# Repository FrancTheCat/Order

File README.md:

# The-Extender
A 5x15 ortholinear keyboard powered by QMK

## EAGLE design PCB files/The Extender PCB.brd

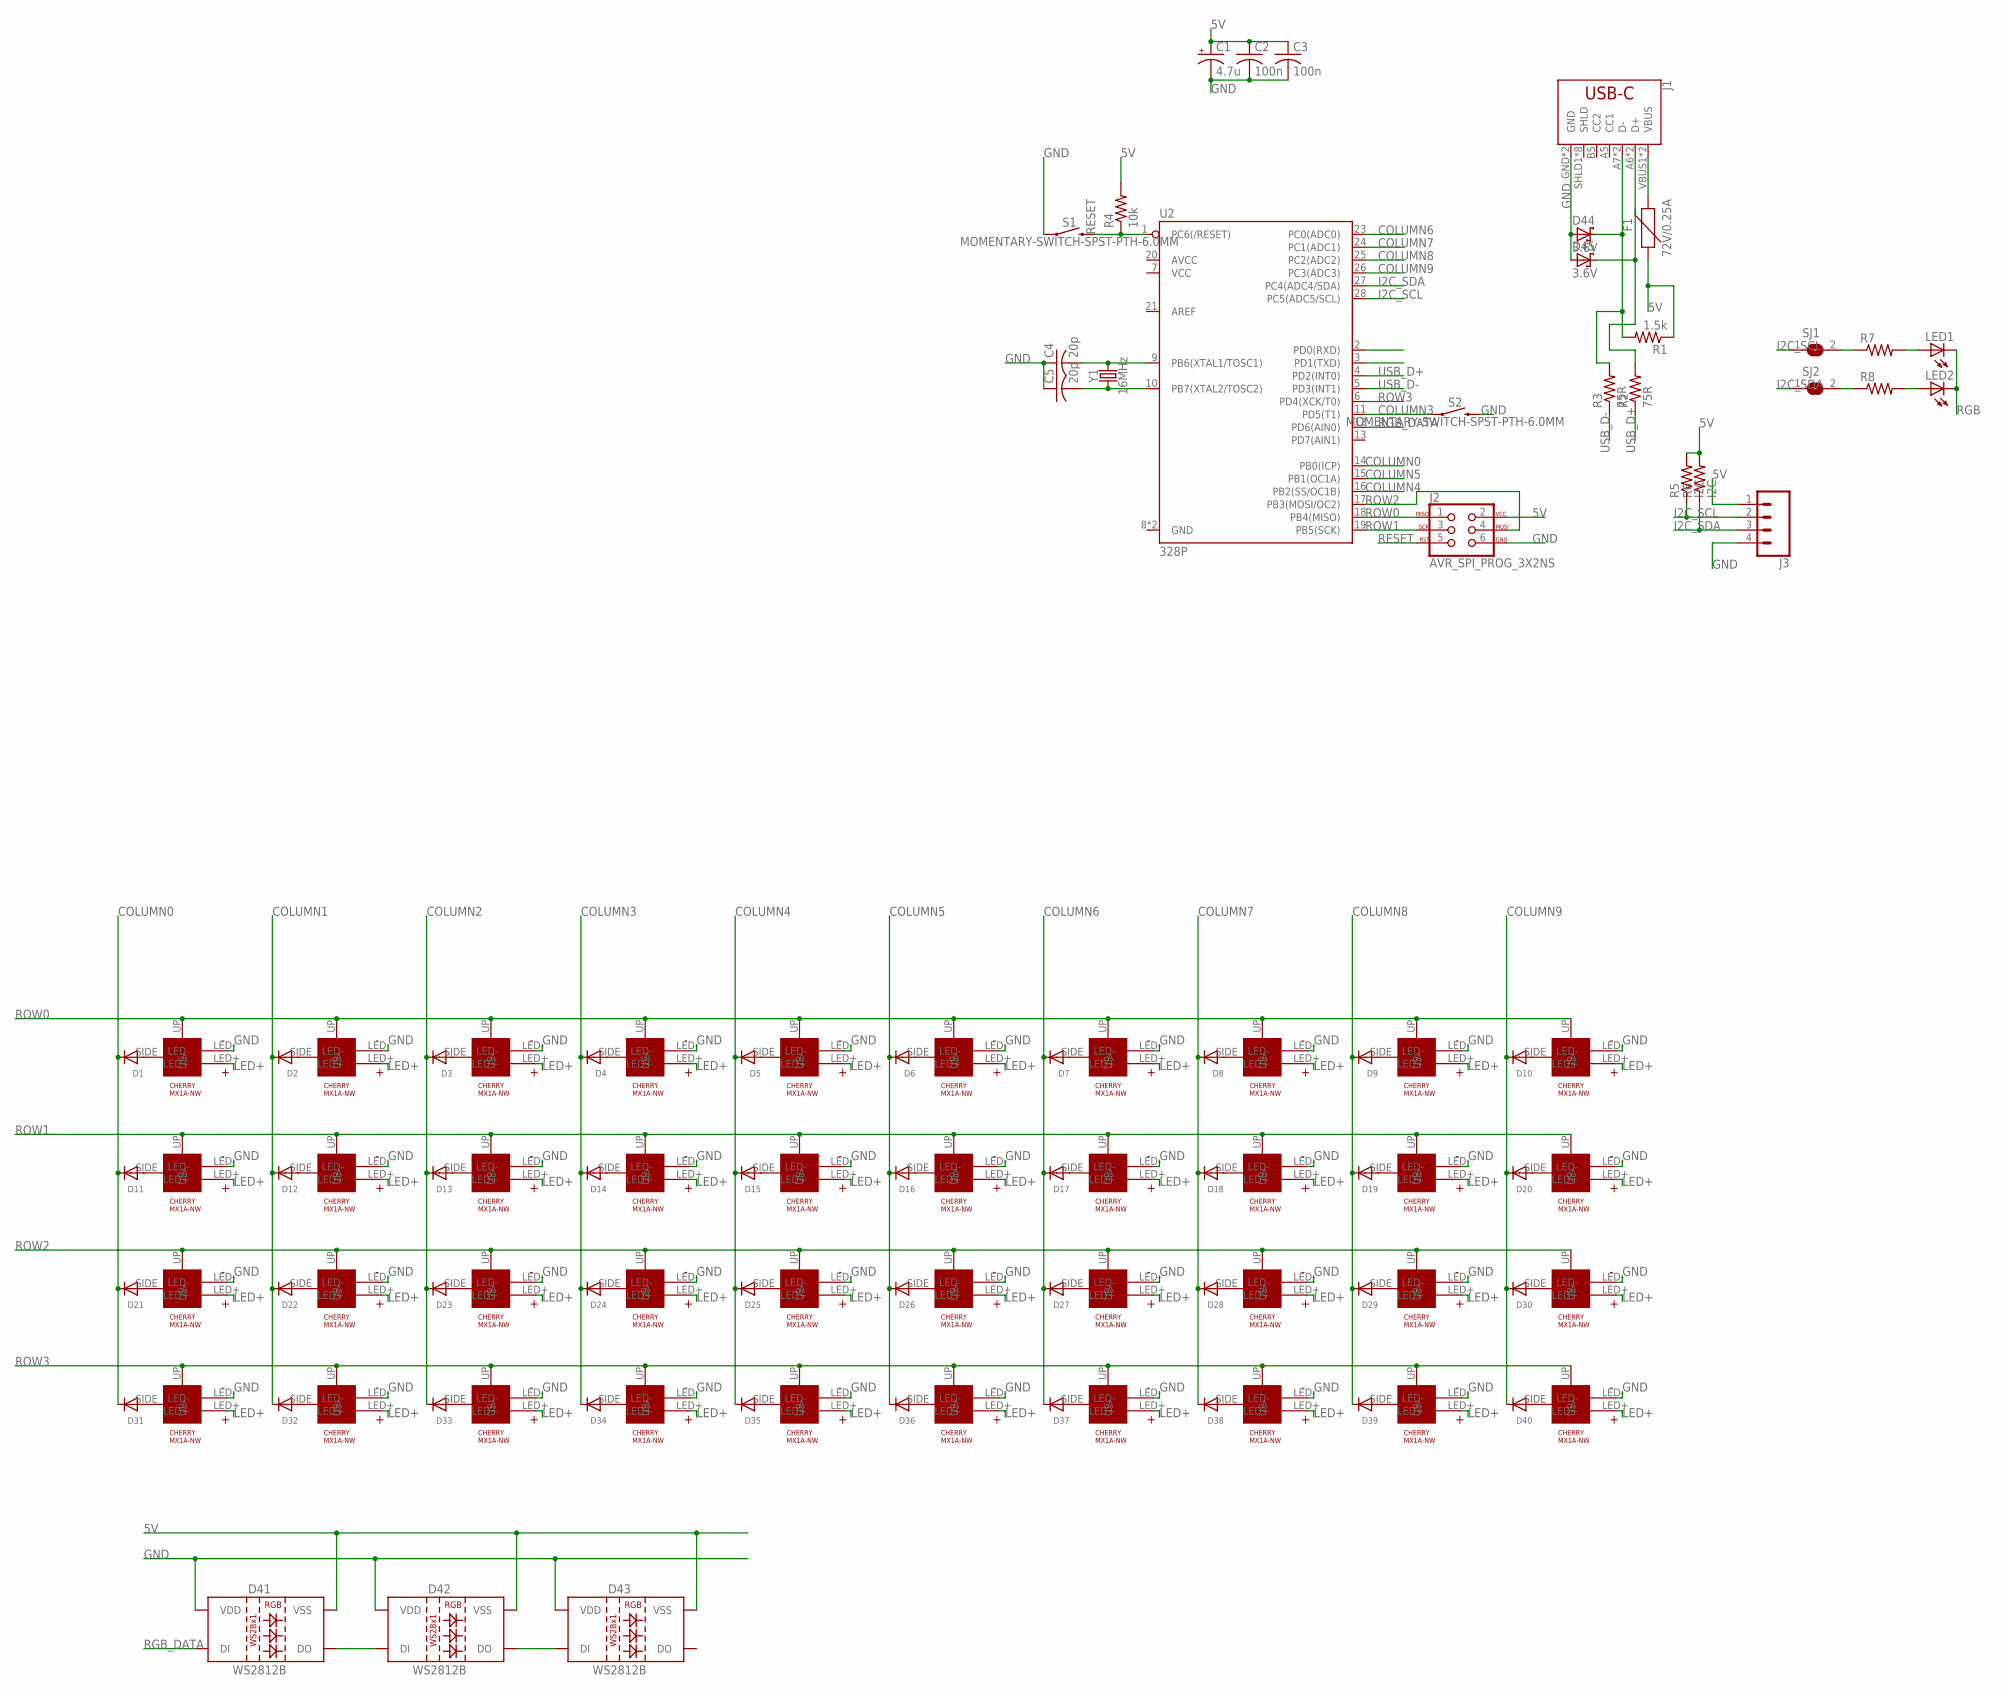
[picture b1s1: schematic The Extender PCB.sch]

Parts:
C1: 4.7u; E2,5-5
C2, C3: 100n; C050-025X075
C4, C5: 20p; C050-025X075
D1, D2, D3, D4, D5, D6, D7, D8, D9, D10, D11, D12, D13, D14, D15, D16, D17, D18, D19, D20, D21, D22, D23, D24, D25, D26, D27, D28, D29, D30, D31, D32, D33, D34, D35, D36, D37, D38, D39, D40: DIODEDO-1N4148; DO-1N4148
D41, D42, D43: WS2812B
D44, D45: 3.6V; DO41-7
F1: 72V/0.25A; PTH
J1: USB_C16PIN; USB-C-16P
J2: AVR_SPI_PROG_3X2NS; 2X3-NS
J3: CONN_04; 1X04
LED1, LED2: LED3MM
R1: 1.5k; 0207/7
R2, R3: 75R; 0207/7
R4: 10k; 0207/5V
R5, R6: I2C; 0207/5V
R7, R8: R-US_0207/5V; 0207/5V
S1, S2: MOMENTARY-SWITCH-SPST-PTH-6.0MM; TACTILE_SWITCH_PTH_6.0MM
SJ1, SJ2: SJ
U2: 328P; DIP28
U$1, U$2, U$3, U$4, U$5, U$6, U$7, U$8, U$9, U$10, U$11, U$12, U$13, U$14, U$15, U$16, U$17, U$18, U$19, U$20, U$21, U$22, U$23, U$24, U$25, U$26, U$27, U$28, U$29, U$30, U$31, U$32, U$33, U$34, U$35, U$36, U$37, U$38, U$39, U$40: CHERRY-MX1A-E1NW-LED; CHERRYMX-NN-LED
Y1: 16MHz; HC49US

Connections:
5V: C1.+, C2.1, C3.1, D41.3 (VSS), D42.3 (VSS), D43.3 (VSS), F1.P$1 (1), J2.2, J3.1, R1.1, R4.2, R5.2, R6.2
COLUMN0: D1.C, D11.C, D21.C, D31.C, U2.14 (PB0(ICP))
COLUMN1: D2.C, D12.C, D22.C, D32.C
COLUMN2: D3.C, D13.C, D23.C, D33.C
COLUMN3: D4.C, D14.C, D24.C, D34.C, S2.1, U2.11 (PD5(T1))
COLUMN4: D5.C, D15.C, D25.C, D35.C, U2.16 (PB2(SS/OC1B))
COLUMN5: D6.C, D16.C, D26.C, D36.C, U2.15 (PB1(OC1A))
COLUMN6: D7.C, D17.C, D27.C, D37.C, U2.23 (PC0(ADC0))
COLUMN7: D8.C, D18.C, D28.C, D38.C, U2.24 (PC1(ADC1))
COLUMN8: D9.C, D19.C, D29.C, D39.C, U2.25 (PC2(ADC2))
COLUMN9: D10.C, D20.C, D30.C, D40.C, U2.26 (PC3(ADC3))
GND: C1.-, C2.2, C3.2, C4.1, C5.1, D41.1 (VDD), D42.1 (VDD), D43.1 (VDD), D44.A, D45.A, J1.GND, J1.GND2 (GND), J2.6, J3.4, S1.1, S2.3 (2), U$1.LED-, U$2.LED-, U$3.LED-, U$4.LED-, U$5.LED-, U$6.LED-, U$7.LED-, U$8.LED-, U$9.LED-, U$10.LED-, U$11.LED-, U$12.LED-, U$13.LED-, U$14.LED-, U$15.LED-, U$16.LED-, U$17.LED-, U$18.LED-, U$19.LED-, U$20.LED-, U$21.LED-, U$22.LED-, U$23.LED-, U$24.LED-, U$25.LED-, U$26.LED-, U$27.LED-, U$28.LED-, U$29.LED-, U$30.LED-, U$31.LED-, U$32.LED-, U$33.LED-, U$34.LED-, U$35.LED-, U$36.LED-, U$37.LED-, U$38.LED-, U$39.LED-, U$40.LED-
I2C_SCL: J3.2, R5.1, SJ1.1, U2.28 (PC5(ADC5/SCL))
I2C_SDA: J3.3, R6.1, SJ2.1, U2.27 (PC4(ADC4/SDA))
LED+: U$1.LED+, U$2.LED+, U$3.LED+, U$4.LED+, U$5.LED+, U$6.LED+, U$7.LED+, U$8.LED+, U$9.LED+, U$10.LED+, U$11.LED+, U$12.LED+, U$13.LED+, U$14.LED+, U$15.LED+, U$16.LED+, U$17.LED+, U$18.LED+, U$19.LED+, U$20.LED+, U$21.LED+, U$22.LED+, U$23.LED+, U$24.LED+, U$25.LED+, U$26.LED+, U$27.LED+, U$28.LED+, U$29.LED+, U$30.LED+, U$31.LED+, U$32.LED+, U$33.LED+, U$34.LED+, U$35.LED+, U$36.LED+, U$37.LED+, U$38.LED+, U$39.LED+, U$40.LED+
unnamed: D1.A, U$1.SIDE (A)
unnamed: D2.A, U$2.SIDE (A)
unnamed: D3.A, U$3.SIDE (A)
unnamed: D4.A, U$4.SIDE (A)
unnamed: D5.A, U$5.SIDE (A)
unnamed: D6.A, U$6.SIDE (A)
unnamed: D7.A, U$7.SIDE (A)
unnamed: D8.A, U$8.SIDE (A)
unnamed: D9.A, U$9.SIDE (A)
unnamed: D10.A, U$10.SIDE (A)
unnamed: D11.A, U$11.SIDE (A)
unnamed: D12.A, U$12.SIDE (A)
unnamed: D13.A, U$13.SIDE (A)
unnamed: D14.A, U$14.SIDE (A)
unnamed: D15.A, U$15.SIDE (A)
unnamed: D16.A, U$16.SIDE (A)
unnamed: D17.A, U$17.SIDE (A)
unnamed: D18.A, U$18.SIDE (A)
unnamed: D19.A, U$19.SIDE (A)
unnamed: D20.A, U$20.SIDE (A)
unnamed: D21.A, U$21.SIDE (A)
unnamed: D22.A, U$22.SIDE (A)
unnamed: D23.A, U$23.SIDE (A)
unnamed: D24.A, U$24.SIDE (A)
unnamed: D25.A, U$25.SIDE (A)
unnamed: D26.A, U$26.SIDE (A)
unnamed: D27.A, U$27.SIDE (A)
unnamed: D28.A, U$28.SIDE (A)
unnamed: D29.A, U$29.SIDE (A)
unnamed: D30.A, U$30.SIDE (A)
unnamed: D31.A, U$31.SIDE (A)
unnamed: D32.A, U$32.SIDE (A)
unnamed: D33.A, U$33.SIDE (A)
unnamed: D34.A, U$34.SIDE (A)
unnamed: D35.A, U$35.SIDE (A)
unnamed: D36.A, U$36.SIDE (A)
unnamed: D37.A, U$37.SIDE (A)
unnamed: D38.A, U$38.SIDE (A)
unnamed: D39.A, U$39.SIDE (A)
unnamed: D40.A, U$40.SIDE (A)
unnamed: D41.2 (DO), D42.4 (DI)
unnamed: D42.2 (DO), D43.4 (DI)
unnamed: F1.P$2 (2), J1.VBUS1 (VBUS), J1.VBUS2 (VBUS)
unnamed: D44.C, J1.A7 (D-), J1.B7 (D-), R1.2, R3.2
unnamed: D45.C, J1.A6 (D+), J1.B6 (D+), R2.2
unnamed: C5.2, U2.10 (PB7(XTAL2/TOSC2)), Y1.1
unnamed: C4.2, U2.9 (PB6(XTAL1/TOSC1)), Y1.2
unnamed: R7.1, SJ1.2
unnamed: LED1.A, R7.2
unnamed: R8.1, SJ2.2
unnamed: LED2.A, R8.2
RESET: J2.5, R4.1, S1.3 (2), U2.1 (PC6(/RESET))
RGB: LED1.K (C), LED2.K (C)
RGB_DATA: D41.4 (DI), U2.12 (PD6(AIN0))
ROW0: J2.1, U2.18 (PB4(MISO)), U$1.UP, U$2.UP, U$3.UP, U$4.UP, U$5.UP, U$6.UP, U$7.UP, U$8.UP, U$9.UP, U$10.UP
ROW1: J2.3, U2.19 (PB5(SCK)), U$11.UP, U$12.UP, U$13.UP, U$14.UP, U$15.UP, U$16.UP, U$17.UP, U$18.UP, U$19.UP, U$20.UP
ROW2: J2.4, U2.17 (PB3(MOSI/OC2)), U$21.UP, U$22.UP, U$23.UP, U$24.UP, U$25.UP, U$26.UP, U$27.UP, U$28.UP, U$29.UP, U$30.UP
ROW3: U2.6 (PD4(XCK/T0)), U$31.UP, U$32.UP, U$33.UP, U$34.UP, U$35.UP, U$36.UP, U$37.UP, U$38.UP, U$39.UP, U$40.UP
USB_D+: R2.1, U2.4 (PD2(INT0))
USB_D-: R3.1, U2.5 (PD3(INT1))

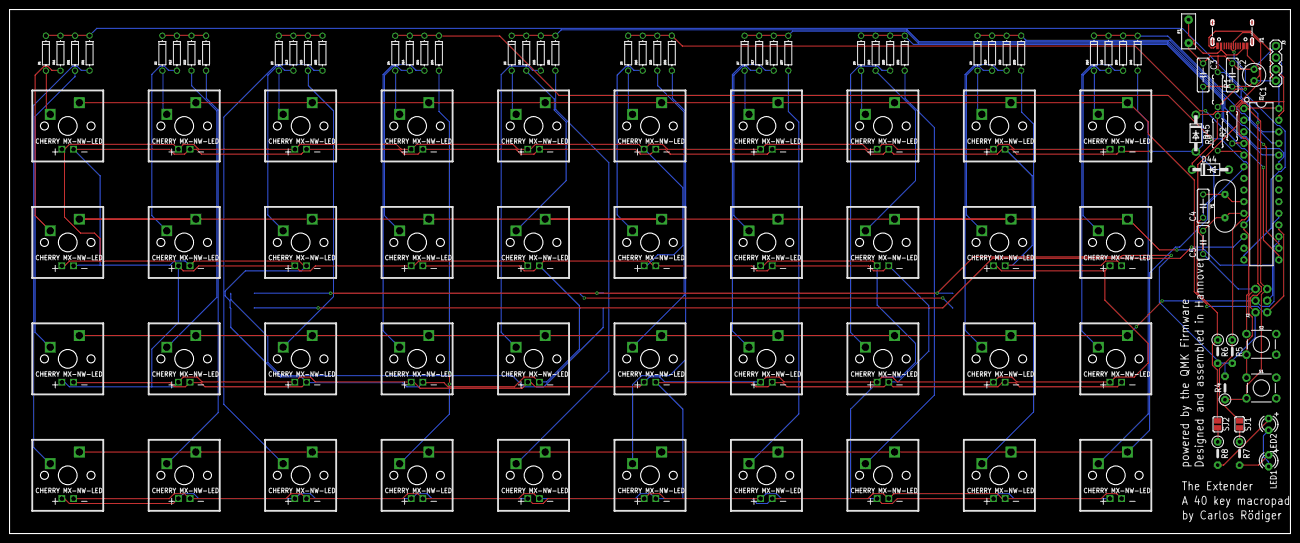
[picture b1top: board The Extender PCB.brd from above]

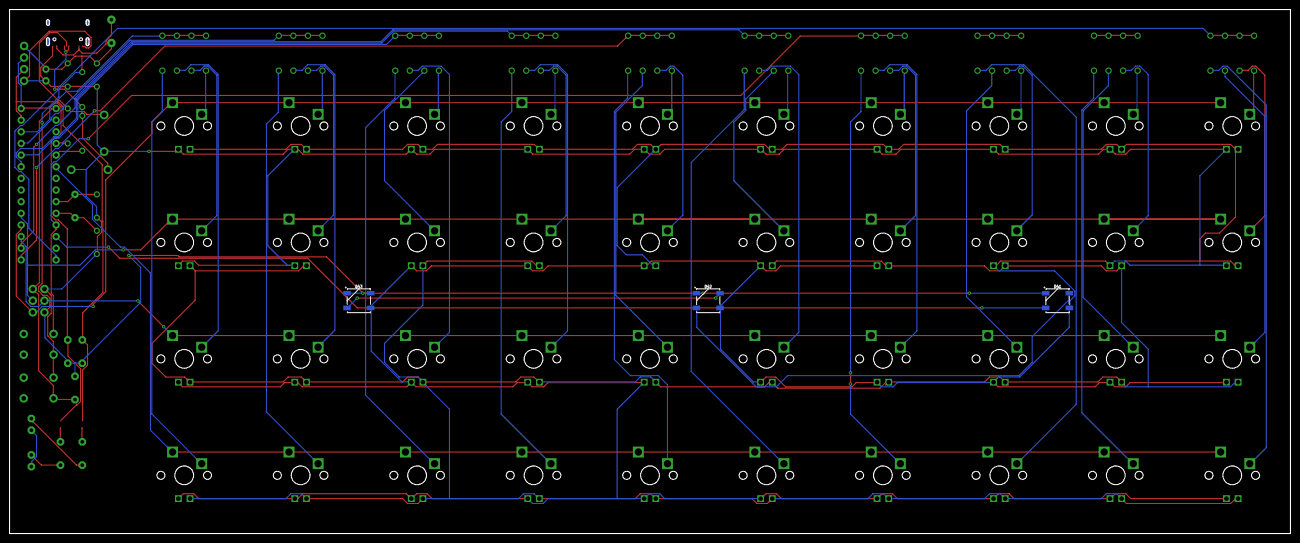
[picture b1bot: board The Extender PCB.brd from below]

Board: 2 copper layers, 279.4 x 114.3 mm, 110 parts (3 on the bottom side), 75 nets.

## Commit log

2019-10-02 First commit
    This is what I have so far! It is only 4x10 right now but i will change it any second!
2019-10-02 Deleted The Extender A 40 Key Macropad By Carlos Rödiger.dxf
    This was an old file for when i was planning to make a 4x10 macropad
2019-10-02 Redesigned the PCB for the final matrix size
    It's now 5x15, the controller was changed to a Teensy 2.0 istead of an AtMEGA 328P
2019-10-05 The first release
    This is what you might call the first release. I will order some prototype PCBs with propably a few minor tweeks!
2019-10-06 This is the first prototype version.
    I made quite a few tweeks to the PCB, a lot of traces were redrawn or moved.
2019-10-14 Renamed the project and deleted some tempoary files
2019-10-14 small PCB improvements
    The +5V traces on the PCB were changed to 20 mil. Some other traces were rerouted to lower the signal distance. The Text on ther PCB was also changed to fit the new name.
2019-10-14 Added Rev 2
    The keyboards dimensions ore now metric and nicely round.
2019-10-15 I am stupid
    I changed the spacing between the keys to the right dimension (19mm) and rearanhged the keyboard. I also added a rotary encoder and a DIP switch.
2019-10-16 now with Traces!
    I added the traces to the new, now less stupid PCB.
2019-10-16 some more improvements
    also added some art
2019-10-17 new LED placement
2019-10-19 Added to QMK badge
    The QMK badge will now be etched to the underside in cooper. I also removed to soldermask to it should look nice and shiny!

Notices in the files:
parts and their libraries:
SparkFun-LED: Licensing: Creative Commons ShareAlike 4.0 International - https://creativecommons.org/licenses/by-sa/4.0
